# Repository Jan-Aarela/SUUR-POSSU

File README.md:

<i>

# Vanha kunnon possu... <b>ISONA</b>

Esimerkiksi kämpän seinälle loistamaan.

! WIP !

  <details>
  <summary><b> SKEEMA  </b></summary>

</details>

<details>
  <summary><b> LEVYT  </b></summary>
<!--  -->
WIP
</details>

## OSALUETTELO
|KPL | MITÄ               | Esim    |
|:---|:---                |---:     |
| 1  | Attiny a861 SOIC   |         |
| 64 | 5mm sin. DIP LED   |         |
| 8  | 110 Ohm 1206        |         |
| 1  | 10 uF SMD           |         |

| Muuta?  |
|:---|
| Joku johto virransyöttä varten |
| Virtalähde 5V DC |
| 2 lyhyttä virtakaapelia levyjen yhdistämiseen|
| Fläshäykseen Arduino ja 6-PIN rima |
| 2 puoleisia piirilevyjä esim. jyrsimällä |
| Jotain materiaalia taustapanelia varten |

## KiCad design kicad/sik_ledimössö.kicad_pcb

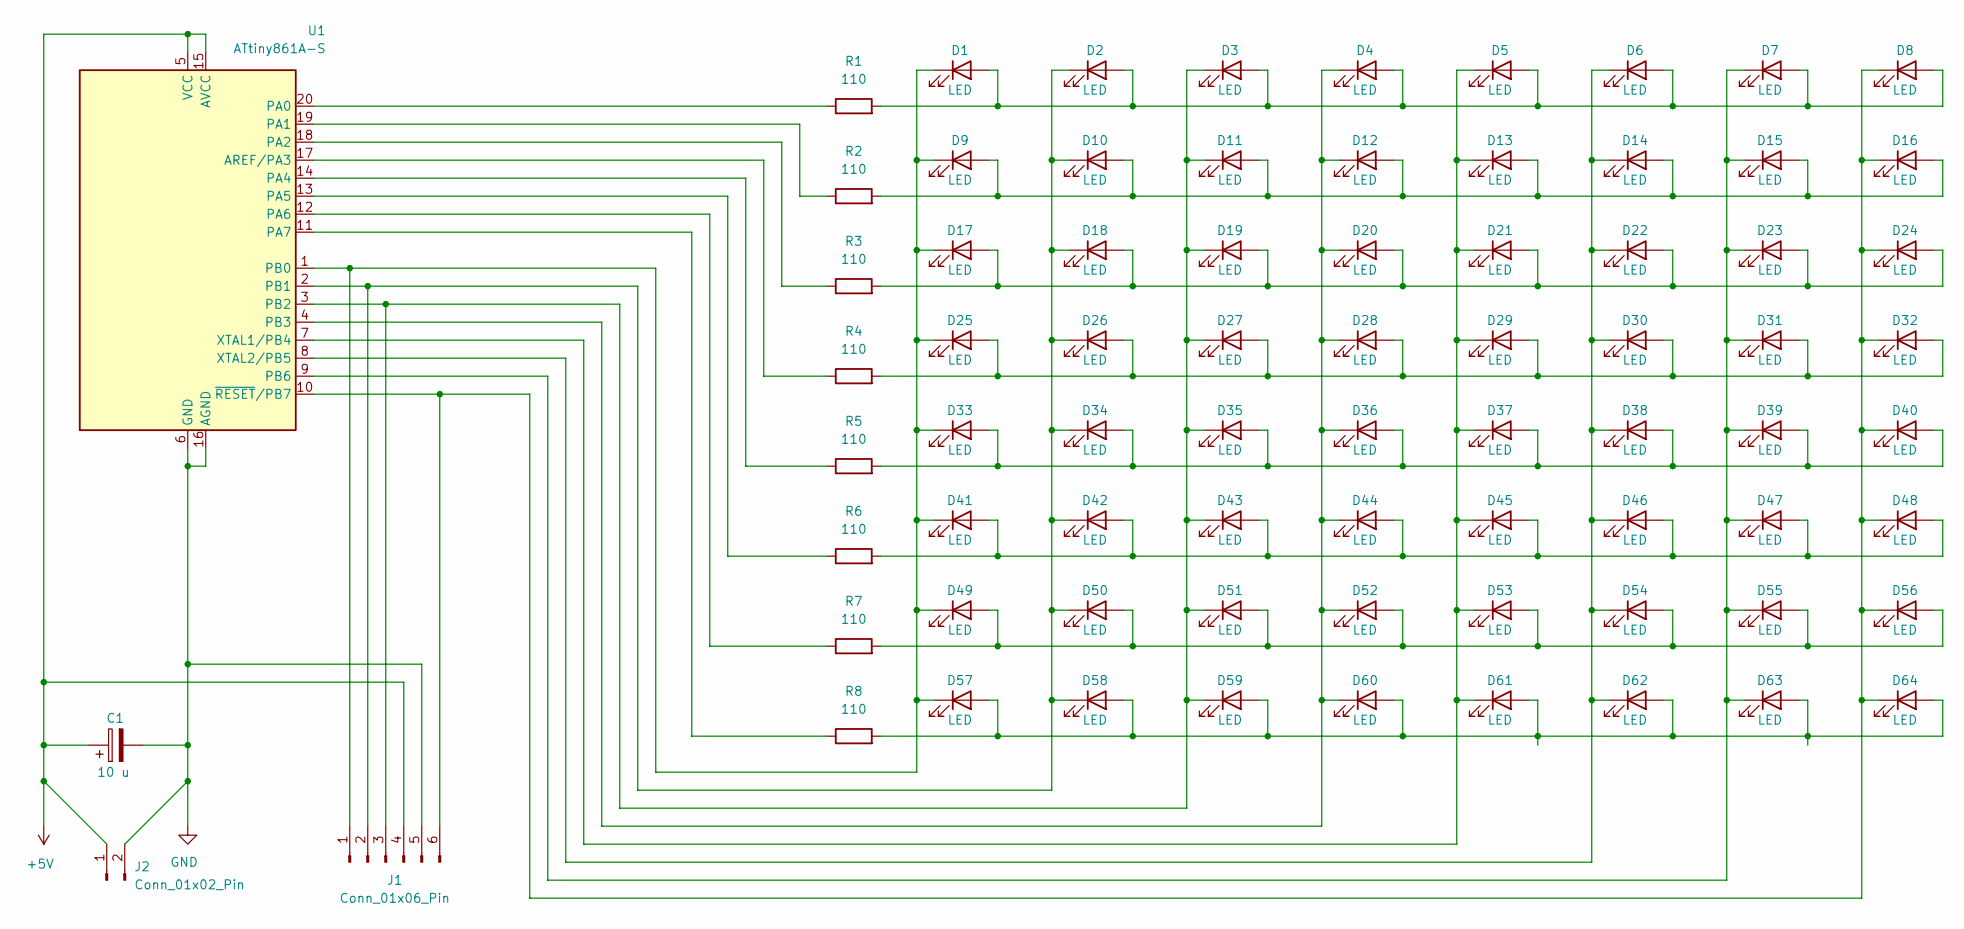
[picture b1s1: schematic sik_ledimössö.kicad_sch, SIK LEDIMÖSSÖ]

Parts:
C1: 10 u; C_1210_3225Metric_Pad1.33x2.70mm_HandSolder
D1, D2, D3, D4, D5, D6, D7, D8, D9, D10, D11, D12, D13, D14, D15, D16, D17, D18, D19, D20, D21, D22, D23, D24, D25, D26, D27, D28, D29, D30, D31, D32, D33, D34, D35, D36, D37, D38, D39, D40, D41, D42, D43, D44, D45, D46, D47, D48, D49, D50, D51, D52, D53, D54, D55, D56, D57, D58, D59, D60, D61, D62, D63, D64: LED; LED_D5.0mm
J1: Conn_01x06_Pin; PinHeader_1x06_P2.00mm_Vertical_SMD_Pin1Left
J2: Conn_01x02_Pin; PinHeader_1x02_P2.00mm_Vertical
R1, R2, R3, R4, R5, R6, R7, R8: 110; R_1206_3216Metric_Pad1.30x1.75mm_HandSolder
U1: ATtiny861A-S; SOIC-20W_7.5x12.8mm_P1.27mm

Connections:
+5V: C1.1, J1.4, J2.1, U1.5 (VCC), U1.15 (AVCC)
GND: C1.2, J1.5, J2.2, U1.6 (GND), U1.16 (AGND)
unnamed: D1.2 (A), D2.2 (A), D3.2 (A), D4.2 (A), D5.2 (A), D6.2 (A), D7.2 (A), D8.2 (A), R1.2
unnamed: D1.1 (K), D9.1 (K), D17.1 (K), D25.1 (K), D33.1 (K), D41.1 (K), D49.1 (K), D57.1 (K), J1.1, U1.1 (PB0)
unnamed: D9.2 (A), D10.2 (A), D11.2 (A), D12.2 (A), D13.2 (A), D14.2 (A), D15.2 (A), D16.2 (A), R2.2
unnamed: D2.1 (K), D10.1 (K), D18.1 (K), D26.1 (K), D34.1 (K), D42.1 (K), D50.1 (K), D58.1 (K), J1.2, U1.2 (PB1)
unnamed: D3.1 (K), D11.1 (K), D19.1 (K), D27.1 (K), D35.1 (K), D43.1 (K), D51.1 (K), D59.1 (K), J1.3, U1.3 (PB2)
unnamed: D4.1 (K), D12.1 (K), D20.1 (K), D28.1 (K), D36.1 (K), D44.1 (K), D52.1 (K), D60.1 (K), U1.4 (PB3)
unnamed: D5.1 (K), D13.1 (K), D21.1 (K), D29.1 (K), D37.1 (K), D45.1 (K), D53.1 (K), D61.1 (K), U1.7 (XTAL1/PB4)
unnamed: D6.1 (K), D14.1 (K), D22.1 (K), D30.1 (K), D38.1 (K), D46.1 (K), D54.1 (K), D62.1 (K), U1.8 (XTAL2/PB5)
unnamed: D7.1 (K), D15.1 (K), D23.1 (K), D31.1 (K), D39.1 (K), D47.1 (K), D55.1 (K), D63.1 (K), U1.9 (PB6)
unnamed: D8.1 (K), D16.1 (K), D24.1 (K), D32.1 (K), D40.1 (K), D48.1 (K), D56.1 (K), D64.1 (K), J1.6, U1.10 (~RESET/PB7)
unnamed: D17.2 (A), D18.2 (A), D19.2 (A), D20.2 (A), D21.2 (A), D22.2 (A), D23.2 (A), D24.2 (A), R3.2
unnamed: D25.2 (A), D26.2 (A), D27.2 (A), D28.2 (A), D29.2 (A), D30.2 (A), D31.2 (A), D32.2 (A), R4.2
unnamed: D33.2 (A), D34.2 (A), D35.2 (A), D36.2 (A), D37.2 (A), D38.2 (A), D39.2 (A), D40.2 (A), R5.2
unnamed: D41.2 (A), D42.2 (A), D43.2 (A), D44.2 (A), D45.2 (A), D46.2 (A), D47.2 (A), D48.2 (A), R6.2
unnamed: D49.2 (A), D50.2 (A), D51.2 (A), D52.2 (A), D53.2 (A), D54.2 (A), D55.2 (A), D56.2 (A), R7.2
unnamed: D57.2 (A), D58.2 (A), D59.2 (A), D60.2 (A), D61.2 (A), D62.2 (A), D63.2 (A), D64.2 (A), R8.2
unnamed: R4.1, U1.17 (AREF/PA3)
unnamed: R1.1, U1.20 (PA0)
unnamed: R2.1, U1.19 (PA1)
unnamed: R3.1, U1.18 (PA2)
unnamed: R5.1, U1.14 (PA4)
unnamed: R6.1, U1.13 (PA5)
unnamed: R7.1, U1.12 (PA6)
unnamed: R8.1, U1.11 (PA7)

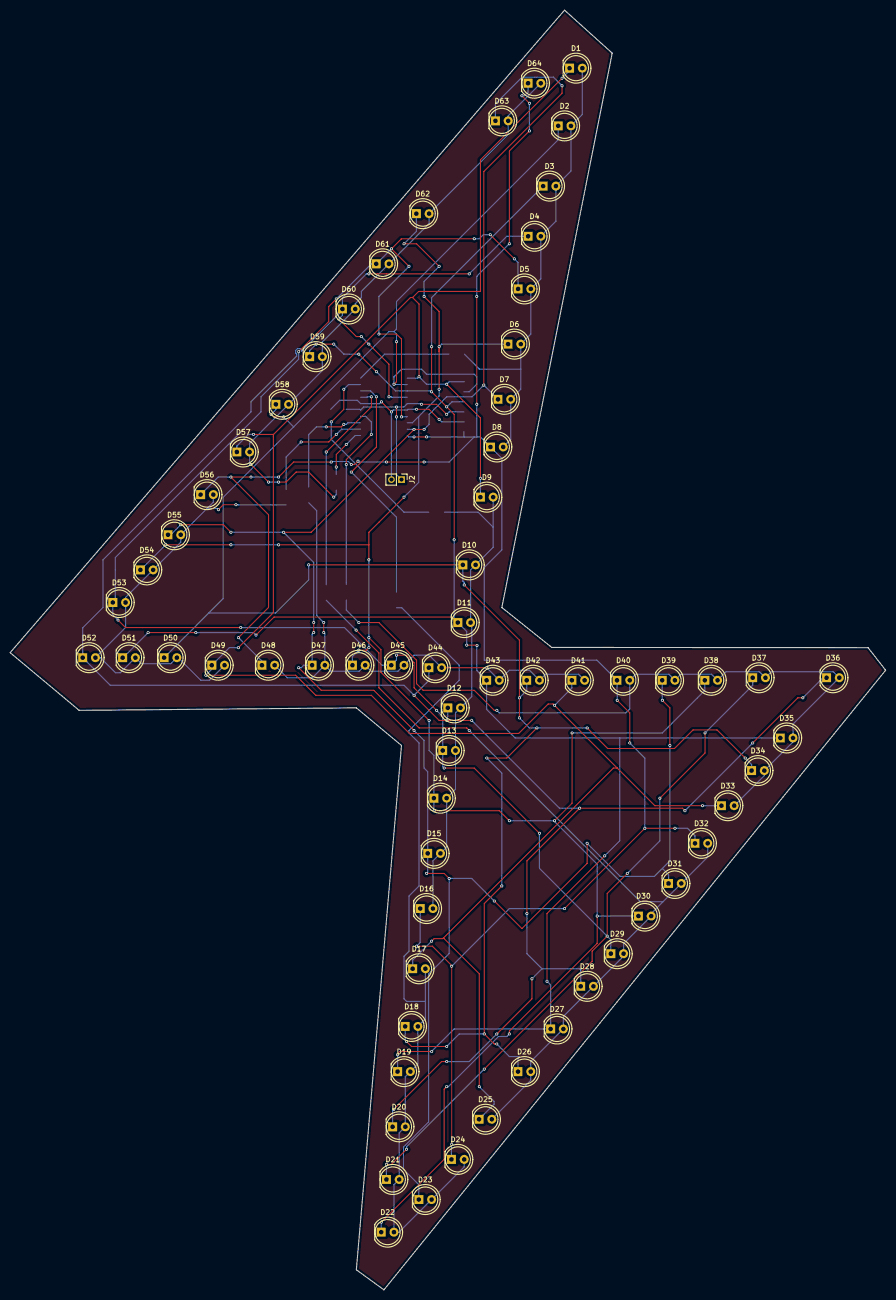
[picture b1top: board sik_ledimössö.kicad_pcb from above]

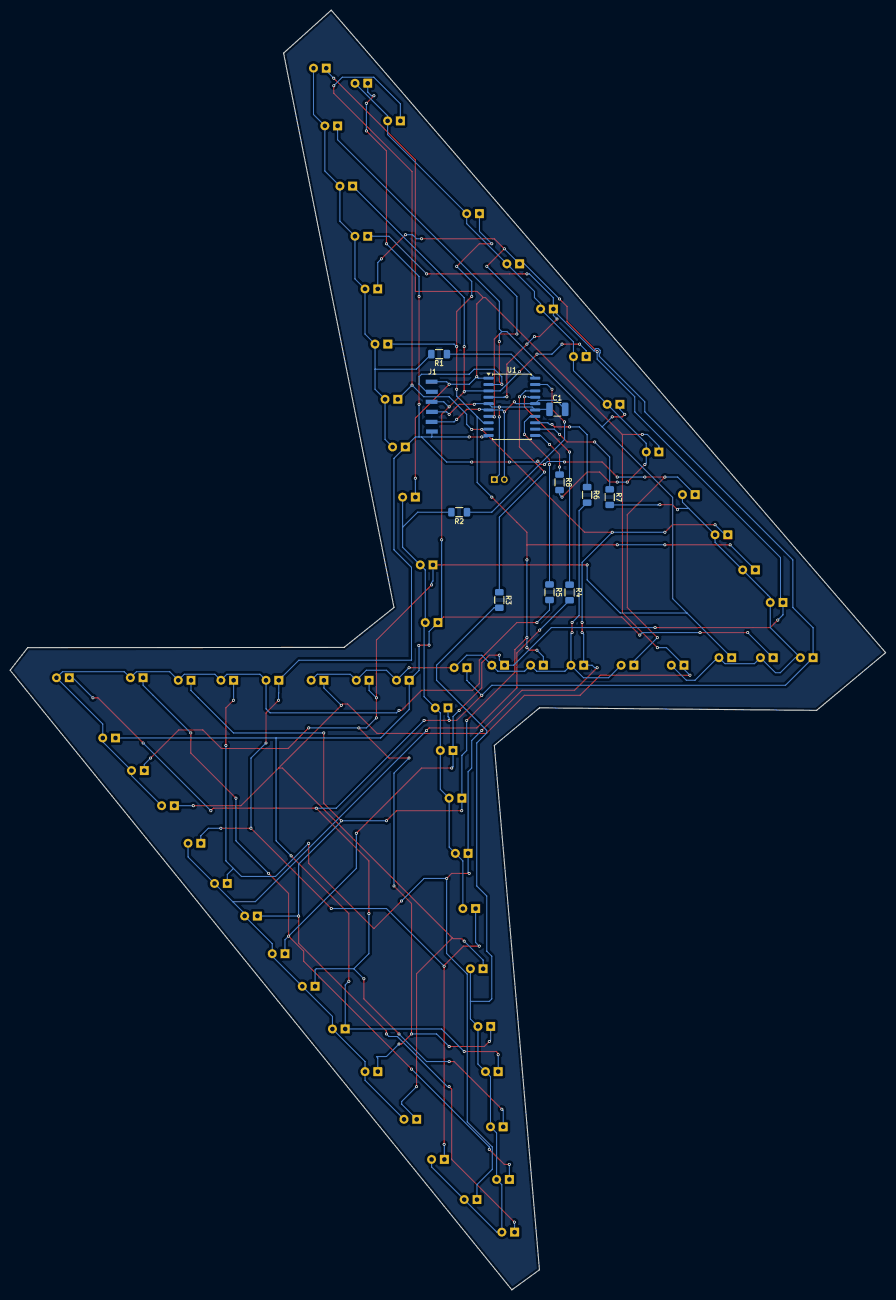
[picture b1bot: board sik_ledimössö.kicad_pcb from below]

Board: 2 copper layers, 174.5 x 255.1 mm, 76 parts (11 on the bottom side), 26 nets.

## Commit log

2025-11-05 Protolevyn leiska valmis*
2025-11-05 Edistystä*
    Paremman leiskan teko aloitettu.
    Alustavat koodit valmiina.
    Osa kopsattu ja muokattu Elektroniikkakerhon LED-merkki reposta.
    Protolevy kokoonpanossa.
